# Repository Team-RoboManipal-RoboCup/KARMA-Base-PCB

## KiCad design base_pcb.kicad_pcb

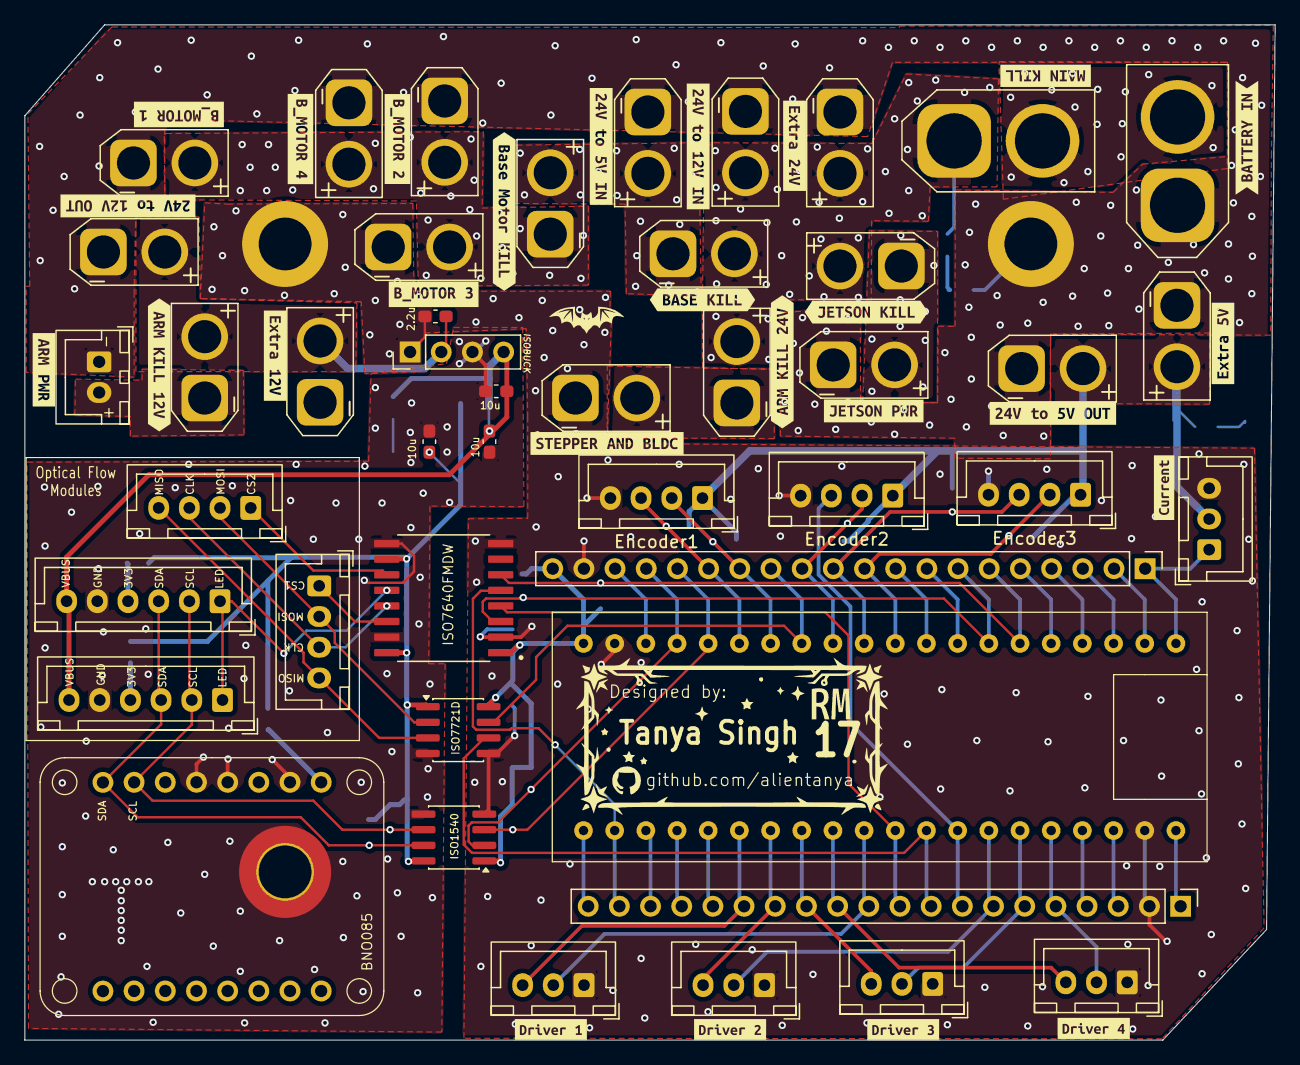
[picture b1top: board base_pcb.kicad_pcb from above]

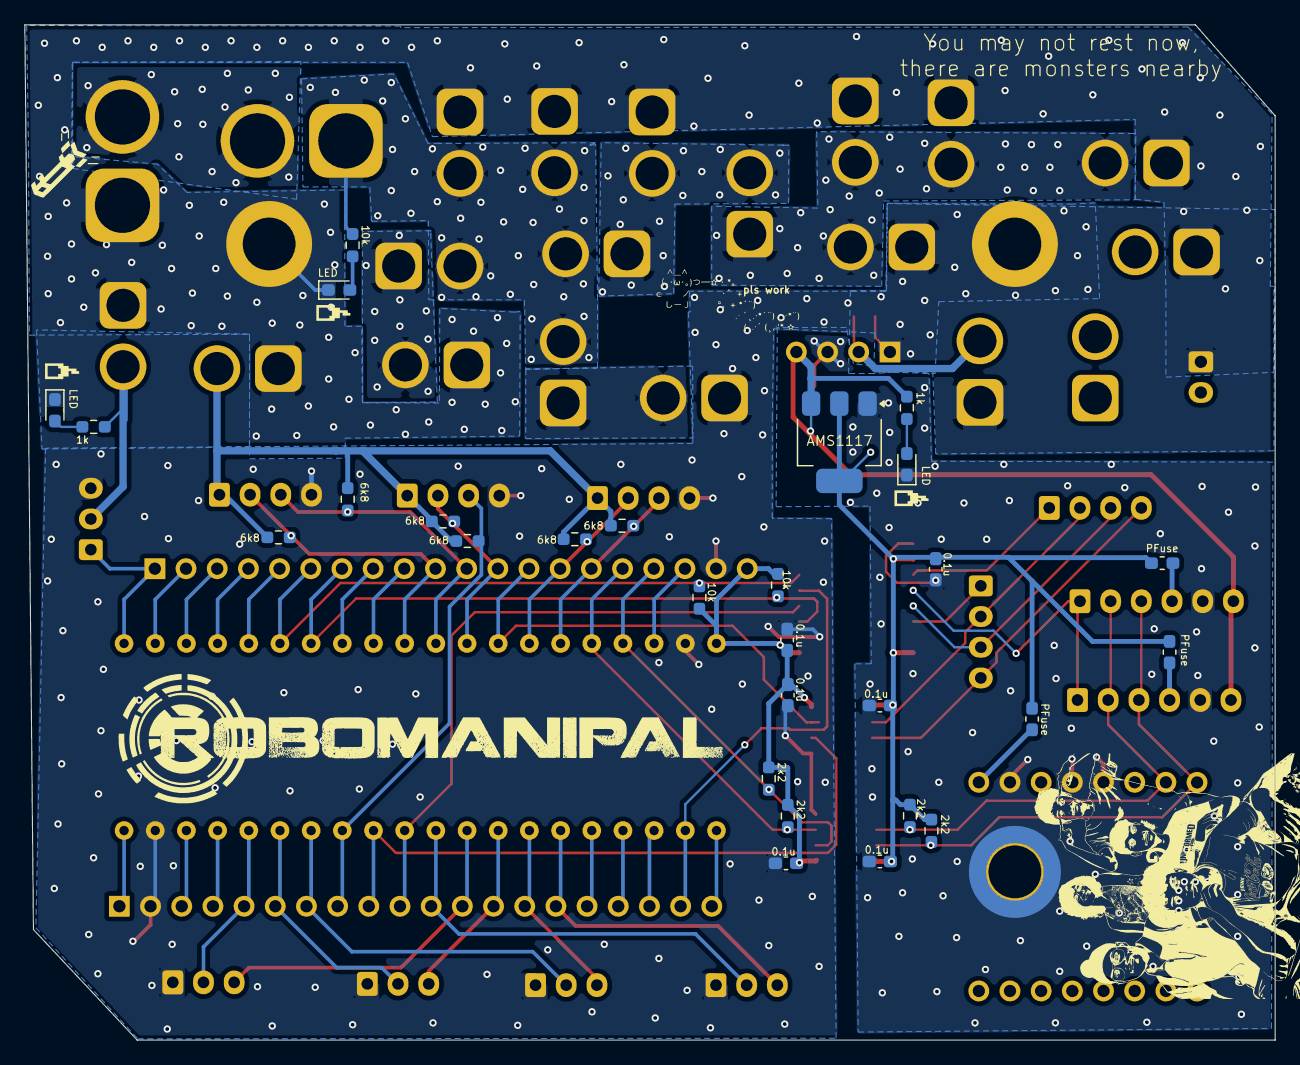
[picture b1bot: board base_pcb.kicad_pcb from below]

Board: 2 copper layers, 101.8 x 82.7 mm, 102 parts (28 on the bottom side), 51 nets.

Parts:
B2: BNO085
C1: 2.2u; C_0603_1608Metric_Pad1.08x0.95mm_HandSolder
C2, C6, C10: 10u; C_0603_1608Metric_Pad1.08x0.95mm_HandSolder
C5, C7, C8, C9, C11, C13: 0.1u; C_0603_1608Metric_Pad1.08x0.95mm_HandSolder
D1, D2, D3: LED; D_0603_1608Metric_Pad1.05x0.95mm_HandSolder
Encoder1, Encoder2, Encoder3: Conn_01x04_Pin; JST_XH_B4B-XH-A_1x04_P2.50mm_Vertical
F1, F2, F3: Polyfuse; Fuse_0603_1608Metric_Pad1.05x0.95mm_HandSolder
H5, H6: MountingHole_Pad; MountingHole_4.3mm_M4_ISO14580_Pad
H8: MountingHole_Pad; MountingHole_4.3mm_M4_DIN965_Pad_TopBottom
IB2: PinHeader_1x04_P2.54mm_Vertical
J1, J2: Conn_01x20_Pin; PinHeader_1x20_P2.54mm_Vertical
J4, J16: Conn_01x04_Pin; JST_XH_B4B-XH-A_1x04_P2.50mm_Vertical
J5, J12: Conn_01x06_Pin; JST_XH_B6B-XH-A_1x06_P2.50mm_Vertical
J6: MOTOR 1 PWR; AMASS_XT30U-M
J7: MOTOR 3 PWR; AMASS_XT30U-M
J8: STEPPER AND BLDC POWER; AMASS_XT30U-M
J9: JETSON POWER; AMASS_XT30U-M
J10: MAIN KILL; AMASS_XT60-M_1x02_P7.20mm_Vertical
J11: BatteryIN; AMASS_XT60-M_1x02_P7.20mm_Vertical
J13: MOTOR 2 PWR; AMASS_XT30U-M
J14: MOTOR 4 PWR; AMASS_XT30U-M
J15: 24V TO 5V BUCK IN; AMASS_XT30U-M
J17: BASE KILL; AMASS_XT30U-M
J18: 24V TO 12V BUCK IN; AMASS_XT30U-M
J21: 24V TO 5V BUCK OUT; AMASS_XT30U-M
J22: 24V TO 12V BUCK OUT; AMASS_XT30U-M
J23: ARM KILL 24V; AMASS_XT30U-M
J24: JETSON KILL; AMASS_XT30U-M
J25: ARM KILL 12V; AMASS_XT30U-M
J26: BASE MOTOR KILL; AMASS_XT30U-M
J27: EXTRA 12V PORT; AMASS_XT30U-M
J28: EXTRA 5V PORT; AMASS_XT30U-M
J29: EXTRA 24V PORT; AMASS_XT30U-M
J30: Conn_01x02_Pin; JST_XH_B2B-XH-A_1x02_P2.50mm_Vertical
J34: Conn_01x03_Pin; JST_XH_B3B-XH-A_1x03_P2.50mm_Vertical
MD1, MD2, MD3, MD4: Conn_01x03_Pin; JST_XH_B3B-XH-A_1x03_P2.50mm_Vertical
R1: 10K; R_0603_1608Metric_Pad0.98x0.95mm_HandSolder
R2, R3: 1K; R_0603_1608Metric_Pad0.98x0.95mm_HandSolder
R4, R5, R6, R7: 2k2; R_0603_1608Metric_Pad0.98x0.95mm_HandSolder
R8, R9: 10k; R_0603_1608Metric_Pad0.98x0.95mm_HandSolder
R11, R12, R13, R14, R15, R16: 6R8K; R_0603_1608Metric_Pad0.98x0.95mm_HandSolder
STM1: STM32F411_BP; blackpill_fp
U1: ISO1540; SOIC-8_3.9x4.9mm_P1.27mm
U2: ISO7721D; SOIC-8_3.9x4.9mm_P1.27mm
U3: ISO7640FMDW; ISO7640FMDW(SOIC127P1030X265-16N)
U4: AMS1117-3.3; SOT-223-3_TabPin2
kibuzzard-6AE9F2F0: G***; kibuzzard-6AE9F2F0
kibuzzard-6AE9F5EA: G***; kibuzzard-6AE9F5EA
kibuzzard-6AE9F5F1: G***; kibuzzard-6AE9F5F1
kibuzzard-6AE9F84A: G***; kibuzzard-6AE9F84A
kibuzzard-6AE9F302: G***; kibuzzard-6AE9F302
kibuzzard-6AE9FCB3: G***; kibuzzard-6AE9FCB3
kibuzzard-6AEB3B53: G***; kibuzzard-6AEB3B53
kibuzzard-6AEB3B63: G***; kibuzzard-6AEB3B63
kibuzzard-6AEB3B74: G***; kibuzzard-6AEB3B74
kibuzzard-6AEB3C4A: G***; kibuzzard-6AEB3C4A
kibuzzard-6AEB3C5F: G***; kibuzzard-6AEB3C5F
kibuzzard-6AEB3C8F: G***; kibuzzard-6AEB3C8F
kibuzzard-6AEB3C9A: G***; kibuzzard-6AEB3C9A
kibuzzard-6AEB3C50: G***; kibuzzard-6AEB3C50
kibuzzard-6AEB3C54: G***; kibuzzard-6AEB3C54
kibuzzard-6AEB3C64: G***; kibuzzard-6AEB3C64
kibuzzard-6AEB3C68: G***; kibuzzard-6AEB3C68
kibuzzard-6AEB3C71: G***; kibuzzard-6AEB3C71
kibuzzard-6AEB3C76: G***; kibuzzard-6AEB3C76
kibuzzard-6AEB3C88: G***; kibuzzard-6AEB3C88
kibuzzard-6AEB3C94: G***; kibuzzard-6AEB3C94
kibuzzard-6AEB3CA7: G***; kibuzzard-6AEB3CA7
kibuzzard-6AEB3CBE: G***; kibuzzard-6AEB3CBE
kibuzzard-6AEB3CCD: G***; kibuzzard-6AEB3CCD
kibuzzard-6AEB3CDA: G***; kibuzzard-6AEB3CDA
kibuzzard-6AEB3CE5: G***; kibuzzard-6AEB3CE5

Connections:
3.3V_ISO: C7.1, C9.1, C10.1, C13.2, F1.1, F2.1, F3.1, R4.1, R5.1, U1.8 (VCC2), U2.1 (VCC1), U3.10 (EN), U3.16 (VCC2), U4.2 (VO)
3.3V_ISO_BNO: B2.16 (3V3), F1.2
3.3V_ISO_LW1: F2.2, J5.4
3.3V_ISO_LW2: F3.2, J12.4
5V_ISO: C2.1, C6.1, IB2.4 (Vo), J5.6, J12.6, R3.1, U4.3 (VI)
12V_ARM: J25.1 (NEG), J30.2
24V_ARM: J8.2 (POS), J23.1 (NEG)
24V_BASE: J15.2 (POS), J17.1 (NEG), J26.2 (POS)
24V_BASE_M: J6.2 (POS), J7.2 (POS), J13.2 (POS), J14.2 (POS), J26.1 (NEG)
24V_BATTERY: J10.2 (POS), J11.2 (POS)
24V_Jetson: J9.2 (POS), J24.1 (NEG)
+3.3V: C5.1, C8.1, C11.2, J1.20, J2.3, R6.1, R7.1, R8.2, R9.1, STM1.3 (3V3), STM1.40 (3V3), U1.1 (VCC1), U2.8 (VCC2), U3.1 (VCC1)
+5V: Encoder1.1, Encoder2.1, Encoder3.1, J21.2 (POS), J28.2 (POS), J34.2, R2.1, R11.2, R12.2, R13.2, R14.2, R15.2, R16.2
+12V: C1.1, IB2.2 (Vin), J22.2 (POS), J25.2 (POS), J27.2 (POS)
+24V: J10.1 (NEG), J17.2 (POS), J18.2 (POS), J23.2 (POS), J24.2 (POS), J29.2 (POS), R1.1
CLK: J4.3, J16.3, U3.13 (OUTB)
CLK_STM: J2.10, STM1.10 (PA5), U3.4 (INB)
CS1: J16.1, U3.14 (OUTA)
CS1_STM: J1.7, R9.2, STM1.27 (PA10), U3.3 (INA)
CS2: J4.1, U3.11 (OUTD)
CS2_STM: J1.6, R8.1, STM1.26 (PA9), U3.6 (IND)
ENC1A: Encoder1.2, J1.14, R11.1, STM1.34 (PB6)
ENC1B: Encoder1.3, J1.15, R12.1, STM1.35 (PB7)
ENC2A: Encoder2.2, J1.12, R14.1, STM1.32 (PB4)
ENC2B: Encoder2.3, J2.8, R13.1, STM1.8 (PA7)
ENC3A: Encoder3.2, J1.10, R15.1, STM1.30 (PA15)
ENC3B: Encoder3.3, J1.11, R16.1, STM1.31 (PB3)
GND: C1.2, C5.2, C8.2, C11.1, D1.1 (K), D2.1 (K), Encoder1.4, Encoder2.4, Encoder3.4, H5.1 (1_1), H6.1 (1_1), IB2.1 (GND1), J1.19, J2.2, J6.1 (NEG), J7.1 (NEG), J8.1 (NEG), J9.1 (NEG), J11.1 (NEG), J13.1 (NEG), J14.1 (NEG), J15.1 (NEG), J18.1 (NEG), J21.1 (NEG), J22.1 (NEG), J27.1 (NEG), J28.1 (NEG), J29.1 (NEG), J30.1, J34.3, MD1.1, MD2.1, MD3.1, MD4.1, STM1.2 (GND), STM1.39 (GND), U1.4 (GND1), U2.5 (GND2), U3.2 (GND1-1), U3.8 (GND1)
ISENSE: J1.1, J34.1, STM1.21 (PB12)
ISOGND: B2.12 (PS0), B2.13 (PS1), B2.15 (GND), C2.2, C6.2, C7.2, C9.2, C10.2, C13.1, D3.1 (K), H8.1 (1_1), IB2.3 (GND2), J5.5, J12.5, U1.5 (GND2), U2.4 (GND1), U3.9 (GND2), U3.15 (GND2-1), U4.1 (GND)
ISO_SCL: B2.10 (SCL), J5.2, J12.2, R5.2, U1.6 (SCL2)
ISO_SDA: B2.9 (SDA), J5.3, J12.3, R4.2, U1.7 (SDA2)
LW_LED: J5.1, J12.1, U3.12 (OUTC)
LW_LED_STM: J2.19, STM1.19 (PC13), U3.5 (INC)
M1DIR: J2.11, MD1.2, STM1.11 (PA4)
M1PWM: J2.15, MD1.3, STM1.15 (PA0)
M2DIR: J2.7, MD2.2, STM1.7 (PB0)
M2PWM: J2.14, MD2.3, STM1.14 (PA1)
M3DIR: J2.6, MD3.2, STM1.6 (PB1)
M3PWM: J2.13, MD3.3, STM1.13 (PA2)
M4DIR: J2.5, MD4.2, STM1.5 (PB2)
M4PWM: J2.12, MD4.3, STM1.12 (PA3)
MISO: J4.4, J16.4, U2.3 (INB)
MISO_STM: J2.9, STM1.9 (PA6), U2.6 (OUTB)
MOSI: J4.2, J16.2, U2.2 (OUTA)
MOSI_STM: J1.13, STM1.33 (PB5), U2.7 (INA)
unnamed: D1.2 (A), R1.2
unnamed: D2.2 (A), R2.2
unnamed: D3.2 (A), R3.2
SCL_STM: J1.16, R7.2, STM1.36 (PB8), U1.3 (SCL1)
SDA_STM: J1.17, R6.2, STM1.37 (PB9), U1.2 (SDA1)
